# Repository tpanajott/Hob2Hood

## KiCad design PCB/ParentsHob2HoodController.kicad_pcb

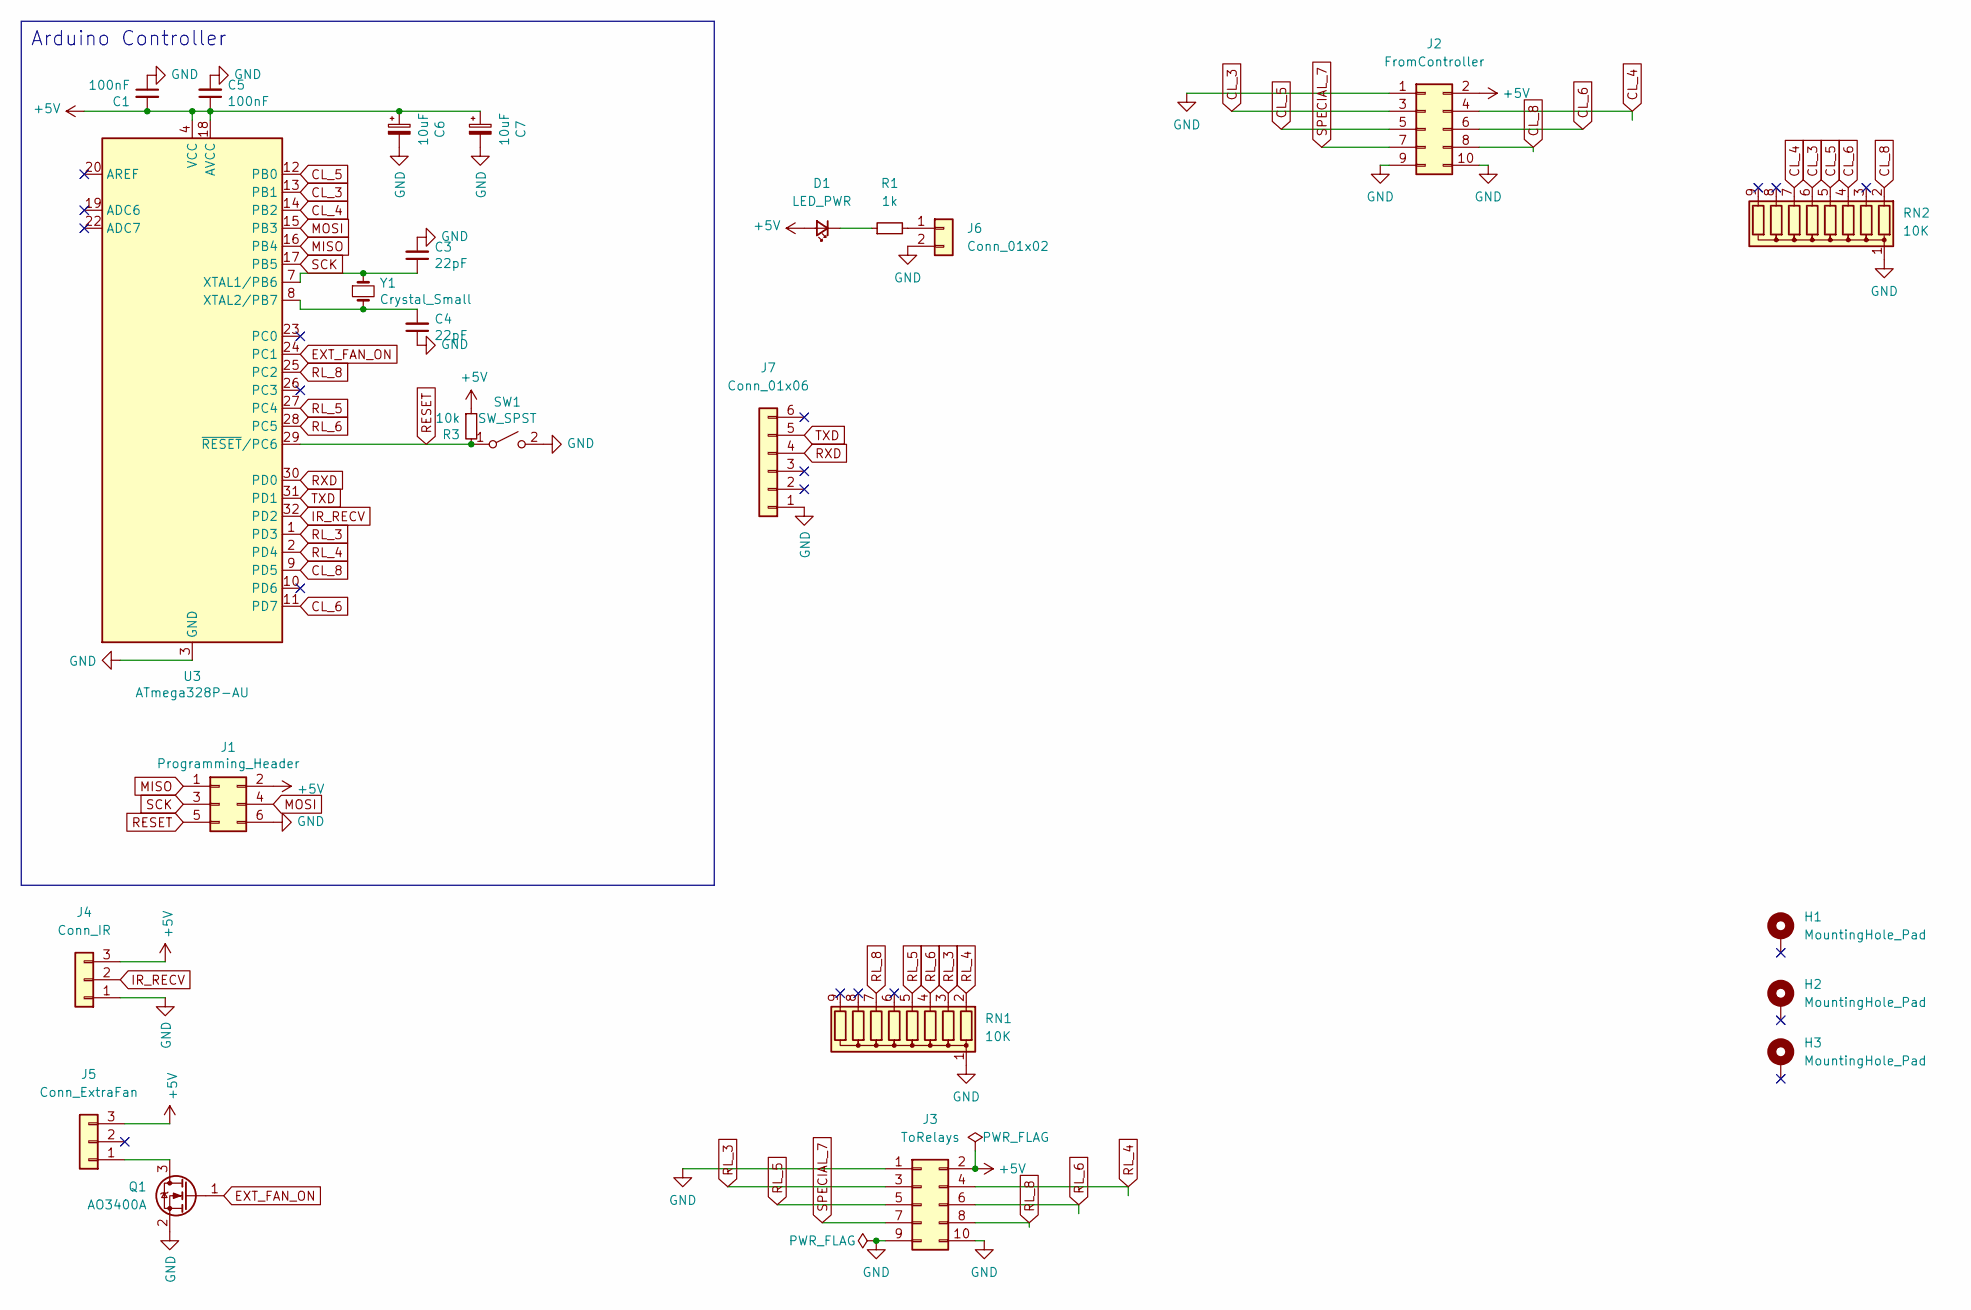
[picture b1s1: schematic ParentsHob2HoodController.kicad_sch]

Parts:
C1, C5: 100nF; C_0805_2012Metric_Pad1.18x1.45mm_HandSolder; LCSC C49678
C3, C4: 22pF; C_0805_2012Metric_Pad1.18x1.45mm_HandSolder; LCSC C24658
C6, C7: 10uF; CP_Radial_D4.0mm_P1.50mm; LCSC C694328
D1: LED_PWR; LED_1206_3216Metric
H1, H2, H3: MountingHole_Pad; MountingHole_3.2mm_M3_DIN965_Pad
J1: Programming_Header; IDC-Header_2x03_P2.54mm_Vertical; LCSC C11214
J2: FromController; IDC-Header_2x05_P2.54mm_Vertical
J3: ToRelays; IDC-Header_2x05_P2.54mm_Vertical
J4: Conn_IR; TerminalBlock_Phoenix_MKDS-3-3-5.08_1x03_P5.08mm_Horizontal
J5: Conn_ExtraFan; TerminalBlock_Phoenix_MKDS-3-3-5.08_1x03_P5.08mm_Horizontal
J6: Conn_01x02; PinHeader_1x02_P2.54mm_Vertical
J7: Conn_01x06; PinSocket_1x06_P2.54mm_Vertical
Q1: AO3400A; SOT-23
R1: 1k; LED_1206_3216Metric
R3: 10k; R_0805_2012Metric_Pad1.20x1.40mm_HandSolder; LCSC C25612
RN1, RN2: 10K; R_Array_SIP9; LCSC C8692
SW1: SW_SPST; SW_Push_SPST_NO_Alps_SKRK
U3: ATmega328P-AU; TQFP-32_7x7mm_P0.8mm; LCSC C14877
Y1: Crystal_Small; Crystal_HC49-U_Vertical; LCSC C16212

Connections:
+5V: C1.2, C5.1, C6.1, C7.1, D1.2 (A), J1.2, J2.2, J3.2, J4.3, J5.3, R3.1, U3.4 (VCC), U3.6 (VCC), U3.18 (AVCC)
CL_3: J2.3, RN2.6 (R5), U3.13 (PB1)
CL_4: J2.4, RN2.7 (R6), U3.14 (PB2)
CL_5: J2.5, RN2.5 (R4), U3.12 (PB0)
CL_6: J2.6, RN2.4 (R3), U3.11 (PD7)
CL_8: J2.8, RN2.2 (R1), U3.9 (PD5)
EXT_FAN_ON: Q1.1 (G), U3.24 (PC1)
GND: C1.1, C3.2, C4.1, C5.2, C6.2, C7.2, J1.6, J2.1, J2.9, J2.10, J3.1, J3.9, J3.10, J4.1, J6.2, J7.1, Q1.2 (S), RN1.1 (common), RN2.1 (common), SW1.2 (B), U3.3 (GND), U3.5 (GND), U3.21 (GND)
IR_RECV: J4.2, U3.32 (PD2)
MISO: J1.1, U3.16 (PB4)
MOSI: J1.4, U3.15 (PB3)
unnamed: C3.1, U3.7 (XTAL1/PB6), Y1.1
unnamed: C4.2, U3.8 (XTAL2/PB7), Y1.2
unnamed: D1.1 (K), R1.1
unnamed: J5.1, Q1.3 (D)
unnamed: J6.1, R1.2
RESET: J1.5, R3.2, SW1.1 (A), U3.29 (~RESET/PC6)
RL_3: J3.3, RN1.3 (R2), U3.1 (PD3)
RL_4: J3.4, RN1.2 (R1), U3.2 (PD4)
RL_5: J3.5, RN1.5 (R4), U3.27 (PC4)
RL_6: J3.6, RN1.4 (R3), U3.28 (PC5)
RL_8: J3.8, RN1.7 (R6), U3.25 (PC2)
RXD: J7.4, U3.30 (PD0)
SCK: J1.3, U3.17 (PB5)
SPECIAL_7: J2.7, J3.7
TXD: J7.5, U3.31 (PD1)

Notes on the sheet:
Arduino Controller

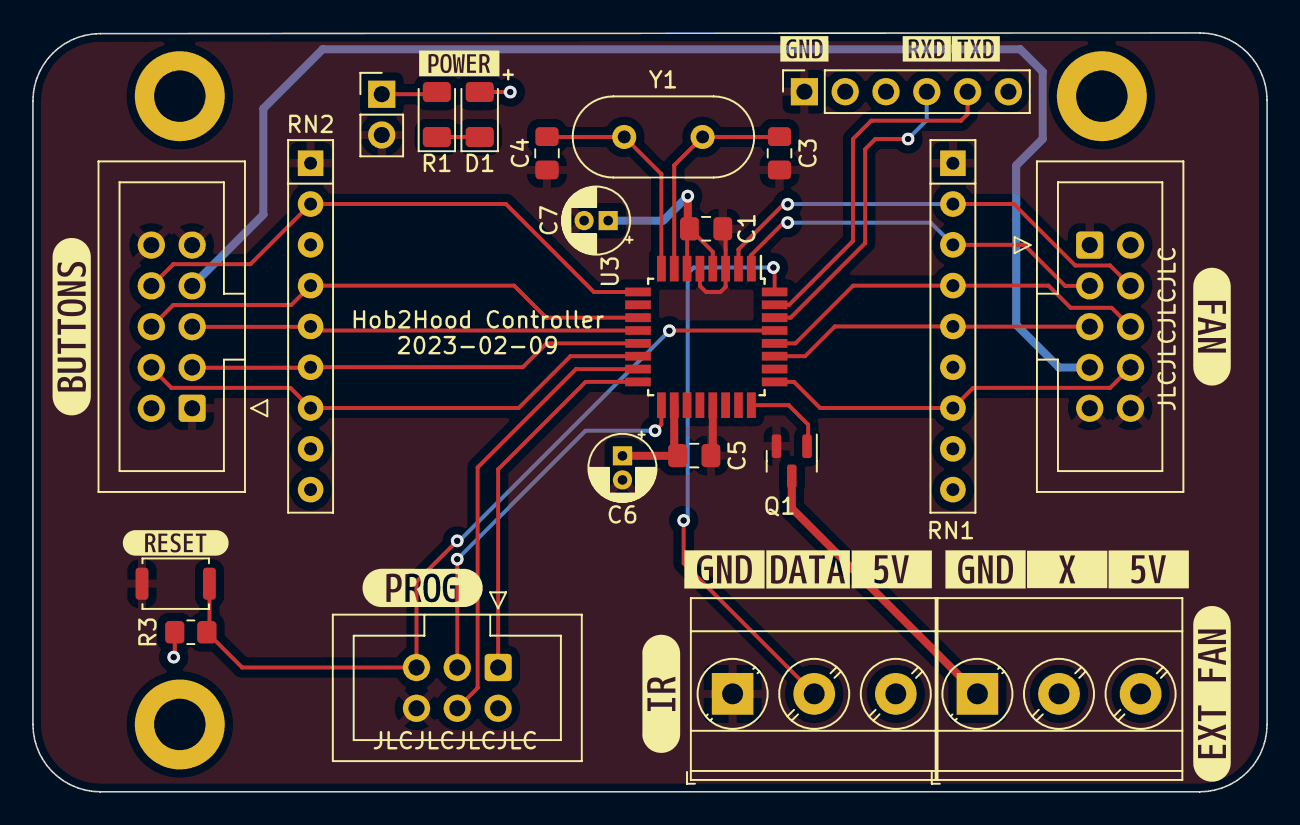
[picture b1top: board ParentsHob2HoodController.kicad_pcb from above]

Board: 2 copper layers, 76.8 x 47.2 mm, 41 parts (0 on the bottom side), 26 nets.

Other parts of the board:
kibuzzard-63DC4623: G***; kibuzzard-63DC4623
kibuzzard-63DDA41D: G***; kibuzzard-63DDA41D
kibuzzard-63DDA454: G***; kibuzzard-63DDA454
kibuzzard-63DDA468: G***; kibuzzard-63DDA468
kibuzzard-63DE4E4C: G***; kibuzzard-63DE4E4C
kibuzzard-63DE4E8B, kibuzzard-63DE4E8B#2: G***; kibuzzard-63DE4E8B
kibuzzard-63DE4E9A, kibuzzard-63DE4E9A#2: G***; kibuzzard-63DE4E9A
kibuzzard-63DE4E81: G***; kibuzzard-63DE4E81
kibuzzard-63DE564F: G***; kibuzzard-63DE564F
kibuzzard-63DE866F: G***; kibuzzard-63DE866F
kibuzzard-63DE867D: G***; kibuzzard-63DE867D
kibuzzard-63DE6880: G***; kibuzzard-63DE6880
kibuzzard-63DE8685: G***; kibuzzard-63DE8685
kibuzzard-63E16F65: G***; kibuzzard-63E16F65

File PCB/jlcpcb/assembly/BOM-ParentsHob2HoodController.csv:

Comment,Designator,Footprint,LCSC
Programming_Header,J1,IDC-Header_2x03_P2.54mm_Vertical,C11214
ATmega328P-AU,U3,TQFP-32_7x7mm_P0.8mm,C14877
Crystal_Small,Y1,Crystal_HC49-U_Vertical,C16212
22pF,"C3,C4",C_0805_2012Metric_Pad1.18x1.45mm_HandSolder,C24658
10k,R3,R_0805_2012Metric_Pad1.20x1.40mm_HandSolder,C25612
100nF,"C1,C5",C_0805_2012Metric_Pad1.18x1.45mm_HandSolder,C49678
10uF,"C6,C7",CP_Radial_D4.0mm_P1.50mm,C694328
10K,"RN1,RN2",R_Array_SIP9,C8692
MountingHole_Pad,H1,MountingHole_3.2mm_M3_DIN965_Pad,
LED_PWR,D1,LED_1206_3216Metric,
Conn_01x02,J6,PinHeader_1x02_P2.54mm_Vertical,
1k,R1,LED_1206_3216Metric,
SW_SPST,SW1,SW_Push_SPST_NO_Alps_SKRK,
MountingHole_Pad,H3,MountingHole_3.2mm_M3_DIN965_Pad,
AO3400A,Q1,SOT-23,
ToRelays,J3,IDC-Header_2x05_P2.54mm_Vertical,
MountingHole_Pad,H2,MountingHole_3.2mm_M3_DIN965_Pad,
FromController,J2,IDC-Header_2x05_P2.54mm_Vertical,
Conn_ExtraFan,J5,TerminalBlock_Phoenix_MKDS-3-3-5.08_1x03_P5.08mm_Horizontal,
Conn_01x06,J7,PinSocket_1x06_P2.54mm_Vertical,
Conn_IR,J4,TerminalBlock_Phoenix_MKDS-3-3-5.08_1x03_P5.08mm_Horizontal,

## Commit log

2023-02-04 Updated with actual IR code values
2023-03-05 Created base plate to protect solder joins from metal housing on fan.
2023-03-05 Removed files that were not needed
